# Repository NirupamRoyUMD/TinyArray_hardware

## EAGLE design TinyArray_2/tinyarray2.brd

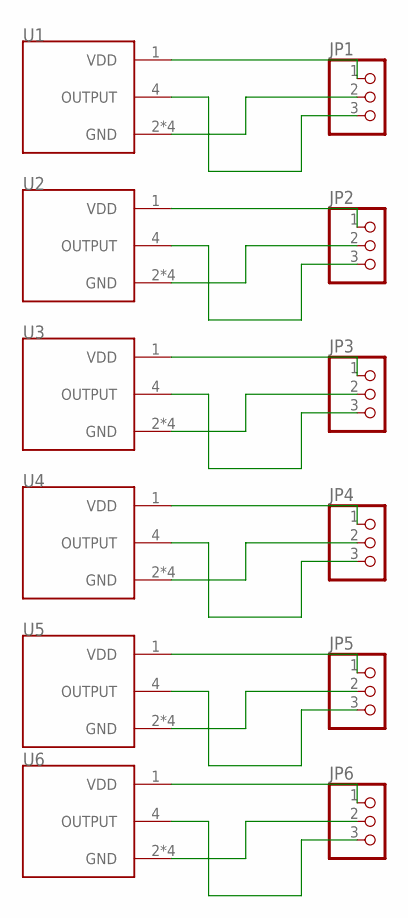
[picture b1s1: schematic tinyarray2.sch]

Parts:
JP1, JP2, JP3, JP4, JP5, JP6: PINHD-1X3; 1X03
U1, U2, U3, U4, U5, U6: CMM-3729AB-38116-TR; XDCR_CMM-3729AB-38116-TR

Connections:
unnamed: JP1.2, U1.2 (GND), U1.3 (GND), U1.5 (GND), U1.6 (GND)
unnamed: JP1.1, U1.1 (VDD)
unnamed: JP1.3, U1.4 (OUTPUT)
unnamed: JP2.2, U2.2 (GND), U2.3 (GND), U2.5 (GND), U2.6 (GND)
unnamed: JP2.1, U2.1 (VDD)
unnamed: JP2.3, U2.4 (OUTPUT)
unnamed: JP3.2, U3.2 (GND), U3.3 (GND), U3.5 (GND), U3.6 (GND)
unnamed: JP3.1, U3.1 (VDD)
unnamed: JP3.3, U3.4 (OUTPUT)
unnamed: JP4.2, U4.2 (GND), U4.3 (GND), U4.5 (GND), U4.6 (GND)
unnamed: JP4.1, U4.1 (VDD)
unnamed: JP4.3, U4.4 (OUTPUT)
unnamed: JP5.2, U5.2 (GND), U5.3 (GND), U5.5 (GND), U5.6 (GND)
unnamed: JP5.1, U5.1 (VDD)
unnamed: JP5.3, U5.4 (OUTPUT)
unnamed: JP6.2, U6.2 (GND), U6.3 (GND), U6.5 (GND), U6.6 (GND)
unnamed: JP6.1, U6.1 (VDD)
unnamed: JP6.3, U6.4 (OUTPUT)

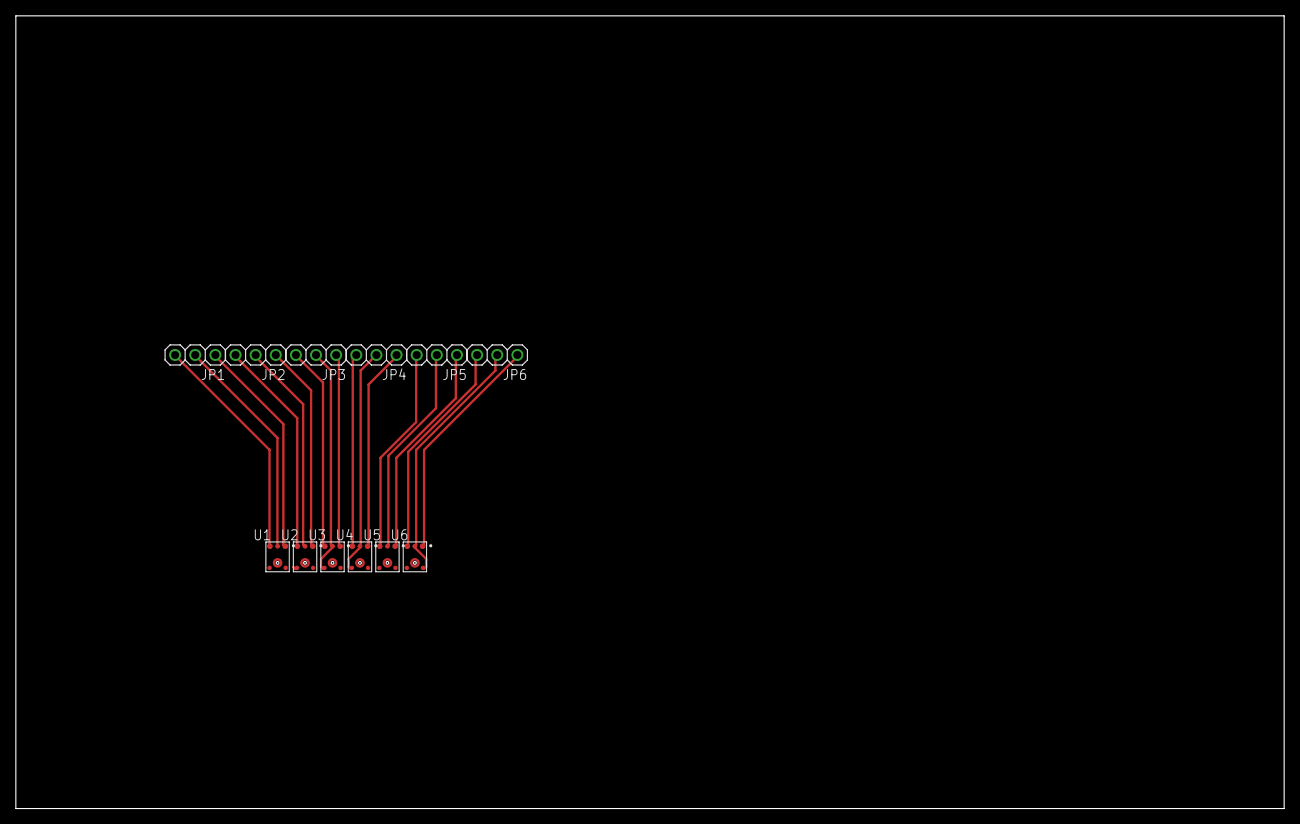
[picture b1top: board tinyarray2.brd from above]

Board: 2 copper layers, 160.0 x 100.0 mm, 12 parts (0 on the bottom side), 18 nets.

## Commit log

2019-08-20 Initial version: Eagle file for 6-element tiny microphone array.
